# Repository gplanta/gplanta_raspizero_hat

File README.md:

# gplanta_raspizero_hat

## Overview

This project is a Raspberry Pi Zero Sensor and PWM uHAT.
Python App coming soon.

## Features

- **ONEWIRE**: Connect ONEWIRE Sensors.
- **I2C**: Connect I2C Sensors.
- **PWM**: Control 2 PWM signals. PWM1 only GND/PWM. PWM2 with 12V DC input and rpm readout.
- **RELAIS**: Connect 4 Relais.
- **SPI**: Connect a SPI Display.

## BOM

- 3x	1k Resistor 0603
- 1x	3k3 Resistor 0603
- 2x	3.9k Resistor 0603
- 1x	4k7 Resistor 0603
- 1x	100n Capacitor 0603
- 1x	680uF Capacitor 1206
- 1x	CAT24C256
- 1x	PJ-102A
- 2x	IRF7319TRPBF
- 1x	CONN_47053-1000_MOL
- 1x	PinHeader_1x08_P2.54mm_Vertical
- 1x	PinHeader_1x04_P2.54mm_Vertical
- 1x	PinHeader_1x06_P2.54mm_Vertical
- 1x	PinHeader_1x03_P2.54mm_Vertical
- 1x	PinSocket_2x20_P2.54mm_Vertical
- 1x	TerminalBlock_MetzConnect_Type059_RT06302HBWC_1x02_P3.50mm_Horizontal
- 1x	TerminalBlock_MetzConnect_Type059_RT06303HBWC_1x03_P3.50mm_Horizontal
- 1x	TerminalBlock_MetzConnect_Type059_RT06304HBWC_1x04_P3.50mm_Horizontal

## PCB Overview
Side:

Front:

Back:

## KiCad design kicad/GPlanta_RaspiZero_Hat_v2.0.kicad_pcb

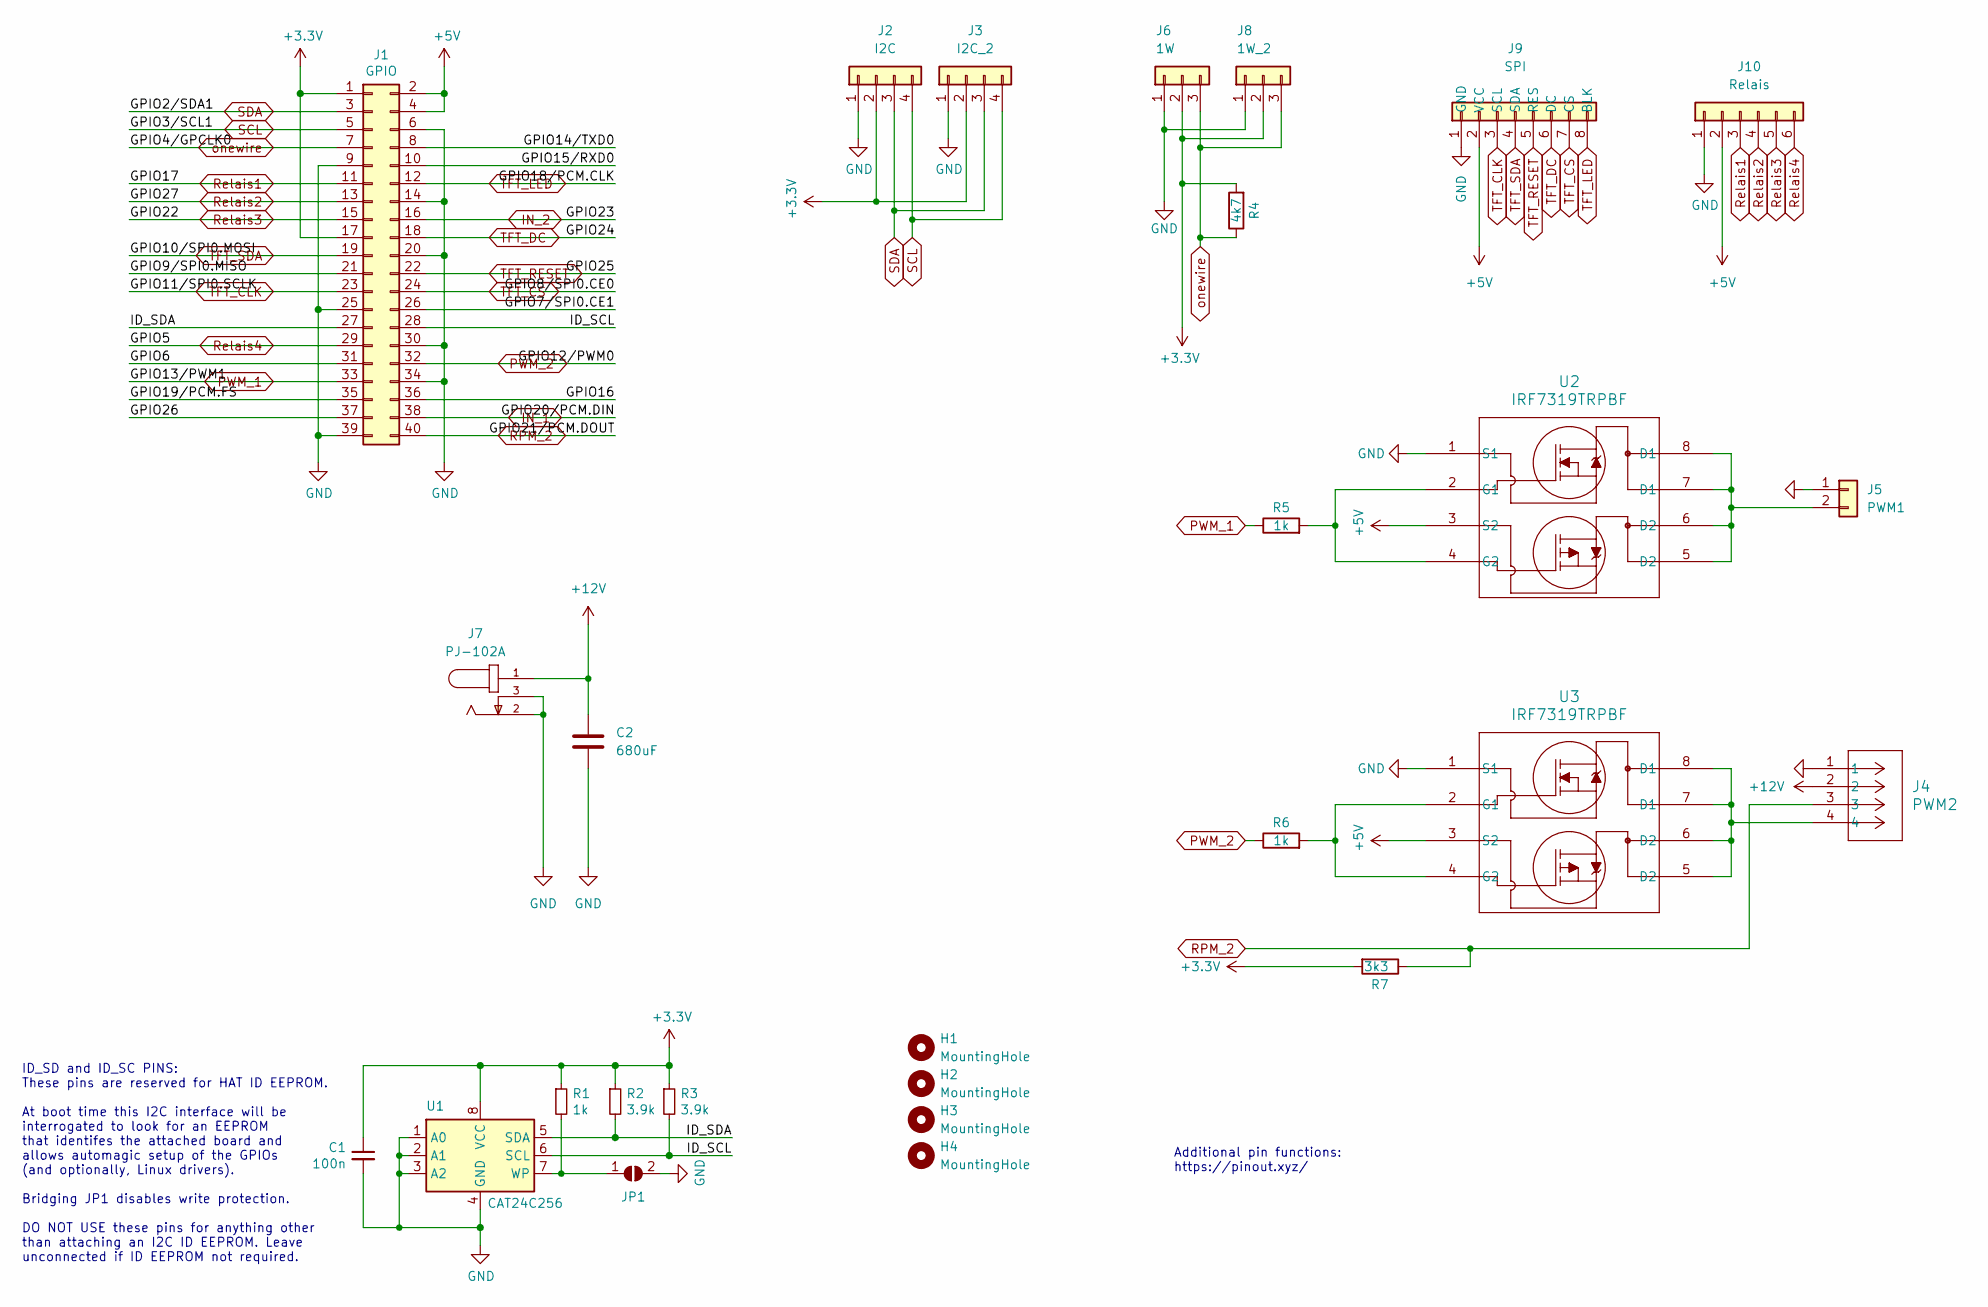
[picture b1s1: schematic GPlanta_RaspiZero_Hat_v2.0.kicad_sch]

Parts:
C1: 100n; C_0603_1608Metric_Pad1.08x0.95mm_HandSolder
C2: 680uF; C_1206_3216Metric_Pad1.33x1.80mm_HandSolder
H1, H2, H3, H4: MountingHole; MountingHole_2.7mm_M2.5
J1: GPIO; PinSocket_2x20_P2.54mm_Vertical
J2: I2C; TerminalBlock_MetzConnect_Type059_RT06304HBWC_1x04_P3.50mm_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
J3: I2C_2; PinHeader_1x04_P2.54mm_Vertical
J4: PWM2; CONN_47053-1000_MOL
J5: PWM1; TerminalBlock_MetzConnect_Type059_RT06302HBWC_1x02_P3.50mm_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
J6: 1W; TerminalBlock_MetzConnect_Type059_RT06303HBWC_1x03_P3.50mm_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
J7: PJ-102A; CUI_PJ-102A; PART_REV 1.03
J8: 1W_2; PinHeader_1x03_P2.54mm_Vertical
J9: SPI; PinHeader_1x08_P2.54mm_Vertical
J10: Relais; PinHeader_1x06_P2.54mm_Vertical
JP1: ID_WP; SolderJumper-2_P1.3mm_Open_RoundedPad1.0x1.5mm
R1, R5, R6: 1k; R_0603_1608Metric_Pad0.98x0.95mm_HandSolder
R2, R3: 3.9k; R_0603_1608Metric_Pad0.98x0.95mm_HandSolder
R4: 4k7; R_0603_1608Metric_Pad0.98x0.95mm_HandSolder
R7: 3k3; R_0603_1608Metric_Pad0.98x0.95mm_HandSolder
U1: CAT24C256; SOIC8-1.27-5X4MM
U2, U3: IRF7319TRPBF; TRANS_IRF7103TRPBF_INF

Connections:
+3V3: C1.1, J1.1, J1.17, J2.2, J3.2, J6.2, J8.2, R1.1, R2.1, R3.1, R4.2, R7.2, U1.8 (VCC)
+5V: J1.2, J1.4, J9.2 (VCC), J10.2, U2.3 (S2), U3.3 (S2)
+12V: C2.1, J4.2, J7.1
/GPIO6: J1.31
/GPIO7/SPI0.CE1: J1.26
/GPIO9/SPI0.MISO: J1.21
/GPIO14/TXD0: J1.8
/GPIO15/RXD0: J1.10
/GPIO16: J1.36
/GPIO19/PCM.FS: J1.35
/GPIO26: J1.37
/ID_SCL: J1.28, R3.2, U1.6 (SCL)
/ID_SDA: J1.27, R2.2, U1.5 (SDA)
GND: C1.2, C2.2, J1.6, J1.9, J1.14, J1.20, J1.25, J1.30, J1.34, J1.39, J2.1, J3.1, J4.1, J5.1, J6.1, J7.2, J7.3, J8.1, J9.1 (GND), J10.1, JP1.2 (B), U1.1 (A0), U1.2 (A1), U1.3 (A2), U1.4 (GND), U2.1 (S1), U3.1 (S1)
IN_1: J1.38
IN_2: J1.16
unnamed: J4.4, U3.5 (D2), U3.6 (D2), U3.7 (D1), U3.8 (D1)
unnamed: J5.2, U2.5 (D2), U2.6 (D2), U2.7 (D1), U2.8 (D1)
unnamed: JP1.1 (A), R1.2, U1.7 (WP)
unnamed: R5.2, U2.2 (G1), U2.4 (G2)
unnamed: R6.2, U3.2 (G1), U3.4 (G2)
PWM_1: J1.33, R5.1
PWM_2: J1.32, R6.1
RPM_2: J1.40, J4.3, R7.1
Relais1: J1.11, J10.3
Relais2: J1.13, J10.4
Relais3: J1.15, J10.5
Relais4: J1.29, J10.6
SCL: J1.5, J2.4, J3.4
SDA: J1.3, J2.3, J3.3
TFT_CLK: J1.23, J9.3 (SCL)
TFT_CS: J1.24, J9.7 (CS)
TFT_DC: J1.18, J9.6 (DC)
TFT_LED: J1.12, J9.8 (BLK)
TFT_RESET: J1.22, J9.5 (RES)
TFT_SDA: J1.19, J9.4 (SDA)
onewire: J1.7, J6.3, J8.3, R4.1

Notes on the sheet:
ID_SD and ID_SC PINS: These pins are reserved for HAT ID EEPROM. At boot time this I2C interface will be interrogated to look for an EEPROM that identifes the attached board and allows automagic setup of the GPIOs (and optionally, Linux drivers). Bridging JP1 disables write protection. DO NOT USE t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
Additional pin functions: https://pinout.xyz/

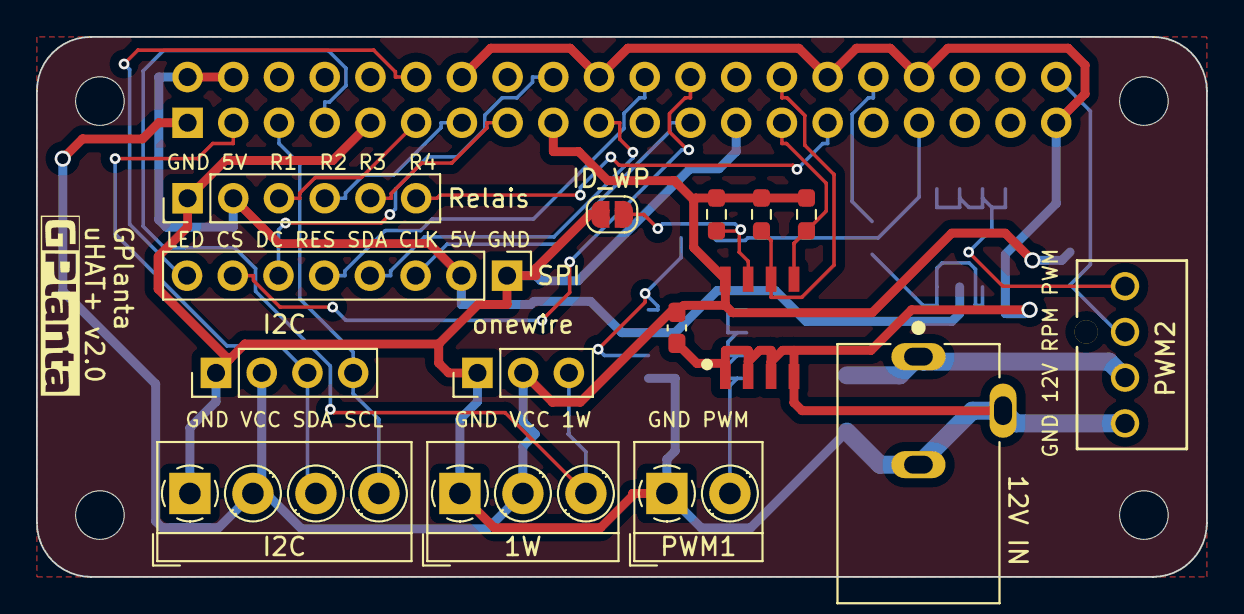
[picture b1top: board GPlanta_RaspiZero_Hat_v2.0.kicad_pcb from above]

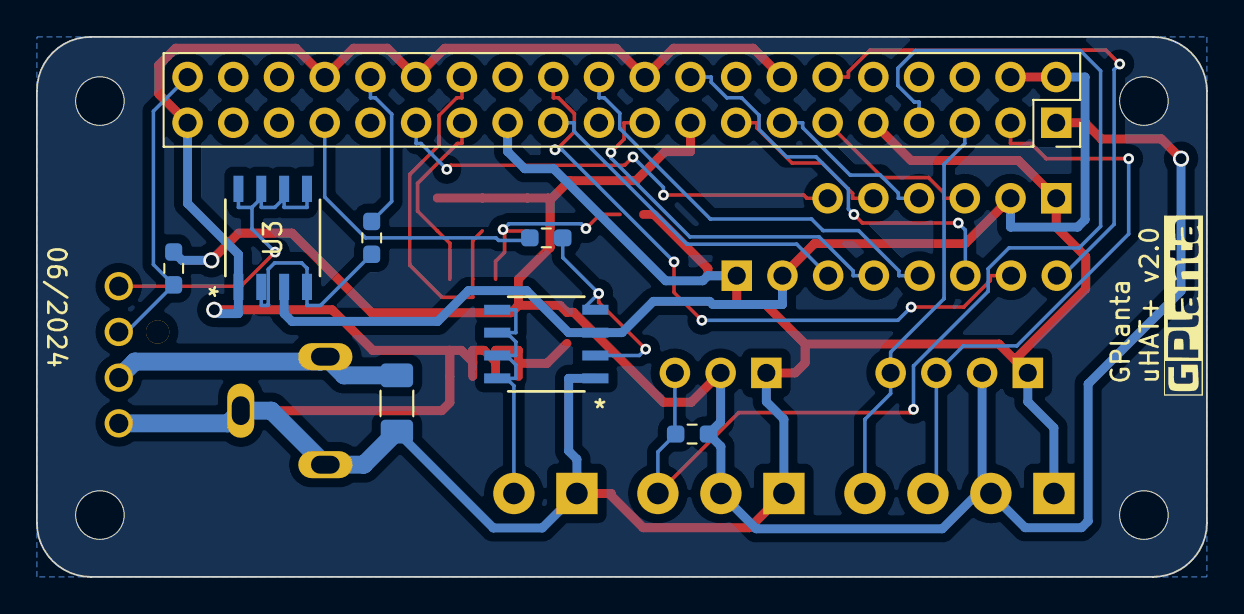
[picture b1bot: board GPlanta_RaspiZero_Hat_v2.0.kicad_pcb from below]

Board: 2 copper layers, 65.0 x 30.0 mm, 29 parts (9 on the bottom side), 27 nets.

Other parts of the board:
G1, G2: LOGO; gplanta_small

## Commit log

2024-07-13 initial release of pcb
